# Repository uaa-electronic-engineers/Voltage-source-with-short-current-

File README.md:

# Voltage-source-with-short-current-

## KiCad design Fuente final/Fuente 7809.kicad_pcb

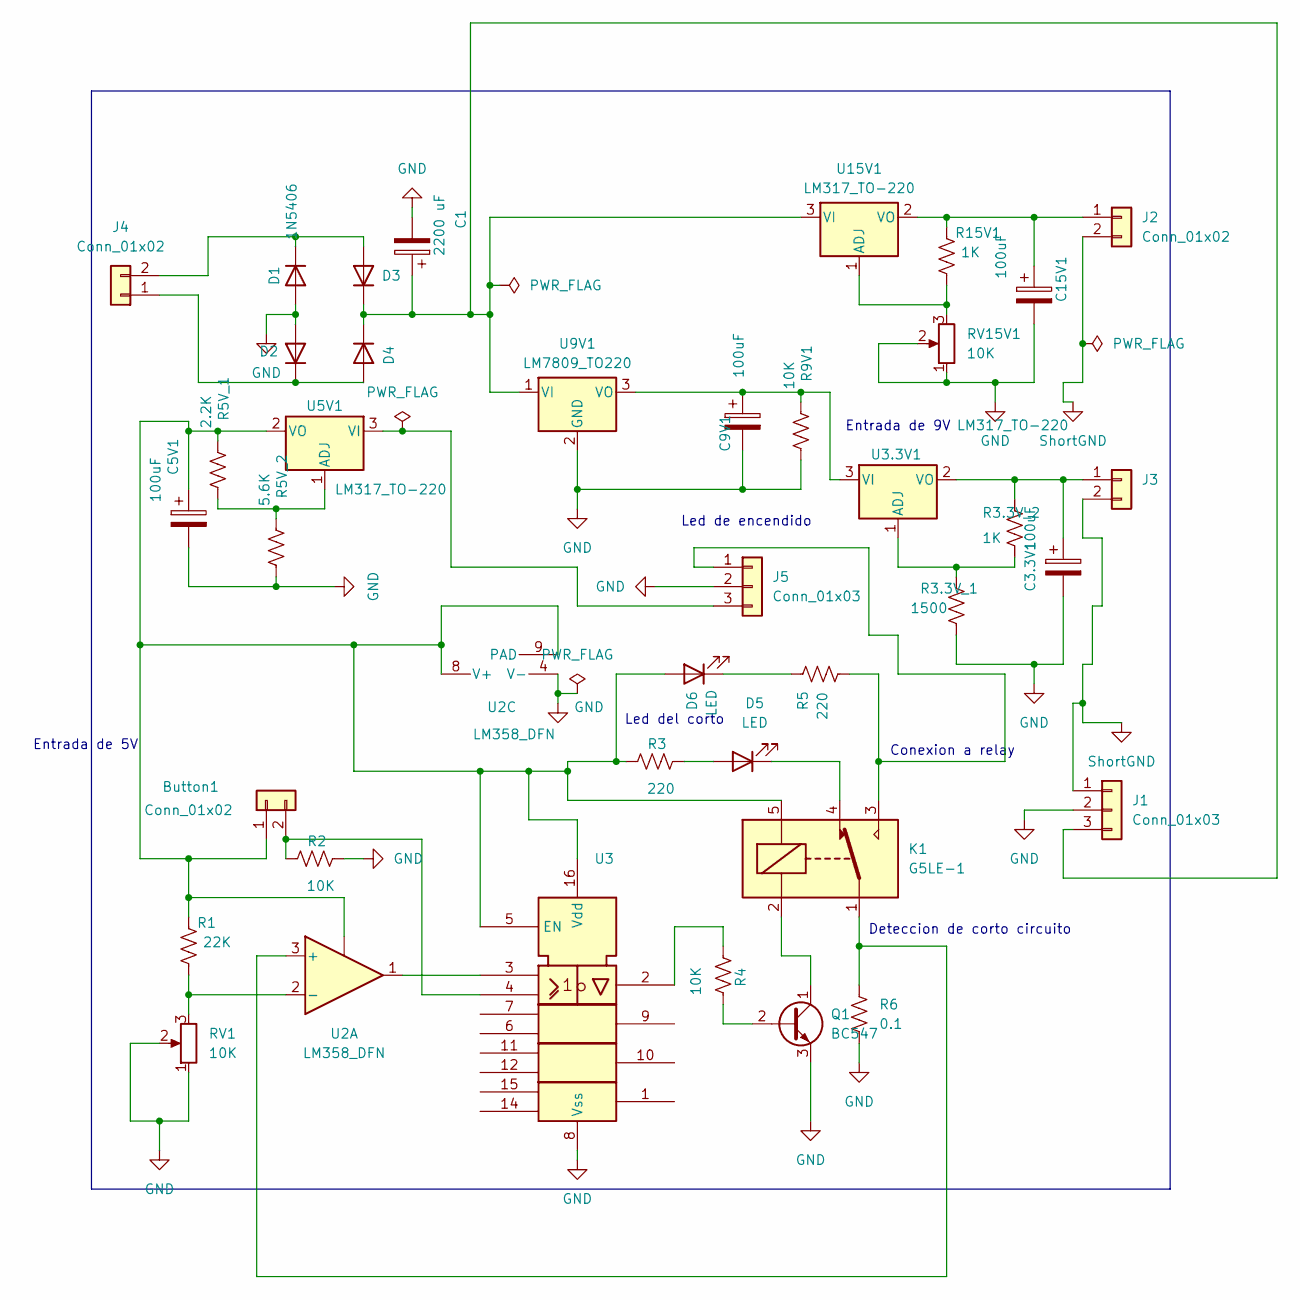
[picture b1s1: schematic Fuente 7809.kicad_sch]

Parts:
Button1: Conn_01x02; TerminalBlock_MaiXu_MX126-5.0-02P_1x02_P5.00mm
C1: 2200 uF; CP_Radial_D14.0mm_P7.50mm
C3.3V1, C5V1, C9V1, C15V1: 100uF; CP_Radial_D8.0mm_P3.50mm
D1, D2, D3, D4: 1N5406; D_DO-201AD_P15.24mm_Horizontal
D5, D6: LED; LED_D5.0mm
J1, J5: Conn_01x03; TerminalBlock_MaiXu_MX126-5.0-03P_1x03_P5.00mm
J2, J3, J4: Conn_01x02; TerminalBlock_MaiXu_MX126-5.0-02P_1x02_P5.00mm
K1: G5LE-1; Relay_SPDT_Omron-G5LE-1
Q1: BC547; TO-92_Inline
R1: 22K; R_Axial_DIN0207_L6.3mm_D2.5mm_P10.16mm_Horizontal
R2, R4, R9V1: 10K; R_Axial_DIN0207_L6.3mm_D2.5mm_P10.16mm_Horizontal
R3, R5: 220; R_Axial_DIN0207_L6.3mm_D2.5mm_P10.16mm_Horizontal
R3.3V_1: 1500; R_Axial_DIN0207_L6.3mm_D2.5mm_P10.16mm_Horizontal
R3.3V_2, R15V1: 1K; R_Axial_DIN0207_L6.3mm_D2.5mm_P10.16mm_Horizontal
R5V_1: 2.2K; R_Axial_DIN0207_L6.3mm_D2.5mm_P10.16mm_Horizontal
R5V_2: 5.6K; R_Axial_DIN0207_L6.3mm_D2.5mm_P10.16mm_Horizontal
R6: 0.1; R_Axial_DIN0411_L9.9mm_D3.6mm_P15.24mm_Horizontal
RV1: 10K; Potentiometer_Bourns_3296W_Vertical
RV15V1: 10K; Potentiometer_Alpha_RD901F-40-00D_Single_Vertical
U2: LM358_DFN; DIP-8_W7.62mm_Socket
U3: 4043; DIP-16_W7.62mm_Socket
U3.3V1, U5V1, U15V1: LM317_TO-220; TO-220-3_Vertical
U9V1: LM7809_TO220; TO-220-3_Vertical

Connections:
GND: C1.2, C3.3V1.2, C5V1.2, C9V1.2, C15V1.2, D1.2 (A), D2.2 (A), J1.2, J5.2, Q1.3 (E), R2.2, R3.3V_1.2, R5V_2.2, R6.1, R9V1.2, RV1.1, RV1.2, RV15V1.1, RV15V1.2, U2.4 (V-), U3.8 (Vss), U9V1.2 (GND)
unnamed: Button1.1, C5V1.1, D6.2 (A), K1.5, R1.1, R3.1, R5V_1.1, U2., U2.8 (V+), U2.9 (PAD), U3.5 (EN), U3.16 (Vdd), U5V1.2 (VO)
unnamed: Button1.2, R2.1, U3.4
unnamed: D1.1 (K), D3.2 (A), J4.2
unnamed: D2.1 (K), D4.2 (A), J4.1
unnamed: C1.1, D3.1 (K), D4.1 (K), J1.3, U9V1.1 (VI), U15V1.3 (VI)
unnamed: D5.2 (A), R3.2
unnamed: D5.1 (K), K1.4
unnamed: D6.1 (K), R5.1
unnamed: C15V1.1, J2.1, R15V1.1, U15V1.2 (VO)
unnamed: C3.3V1.1, J3.1, R3.3V_2.1, U3.3V1.2 (VO)
unnamed: J5.1, K1.3, R5.2
unnamed: J5.3, U5V1.3 (VI)
unnamed: Q1.2 (B), R4.2
unnamed: K1.2, Q1.1 (C)
unnamed: R4.1, U3.2
unnamed: U2.1, U3.3
unnamed: K1.1, R6.2, U2.3 (+)
unnamed: R1.2, RV1.3, U2.2 (-)
unnamed: R3.3V_1.1, R3.3V_2.2, U3.3V1.1 (ADJ)
unnamed: C9V1.1, R9V1.1, U3.3V1.3 (VI), U9V1.3 (VO)
unnamed: R5V_1.2, R5V_2.1, U5V1.1 (ADJ)
unnamed: R15V1.2, RV15V1.3, U15V1.1 (ADJ)
ShortGND: J1.1, J2.2, J3.2

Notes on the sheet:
Entrada de 5V
Conexion a relay
Entrada de 9V
Led del corto
Led de encendido
Deteccion de corto circuito

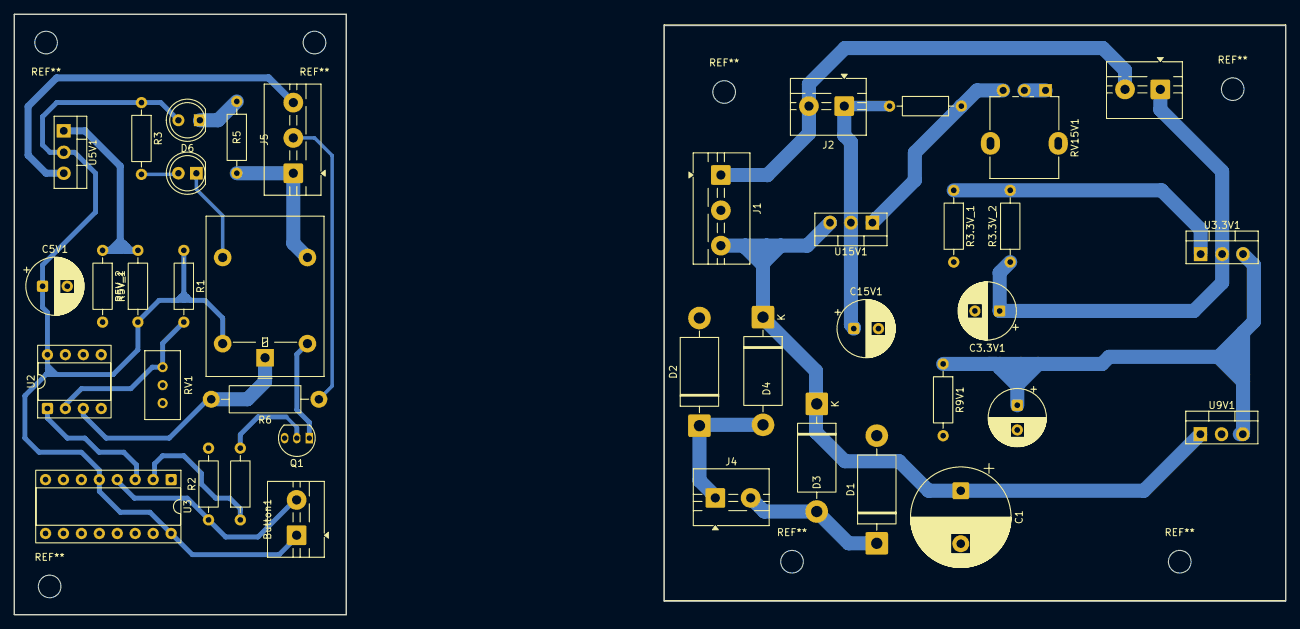
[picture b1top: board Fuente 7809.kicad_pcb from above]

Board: 2 copper layers, 180.0 x 85.0 mm, 39 parts (0 on the bottom side), 24 nets.
